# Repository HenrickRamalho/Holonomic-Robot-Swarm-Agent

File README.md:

# Omnino - Holonomic Agent for Swarm Robots

This project offers robotic technology for technical / scientific work in mobile robotics and swarm robots, using 3D printing tools, printed circuit board making, microcontroller programming, raspberry pi and the embedded implementation of ROS, you will be able to develop your own robotic agent and conduct your research in robotics on an experimental basis.

## Getting Started

To build this project, you must purchase the following bill of materials:

3 x Wheel Omni 1.5Pol

3 x Power Banck Pack for 2 Battery 18650

3 x Motor N20 6Vdc 90RPM and Encoder   

Print attached stl files

### Motor Speed Controller

The speed control of motors of a mobile robot is extremely important for the accomplishment of a good robotics project. This project involves the construction of a microcontrolled circuit for the speed control of each holonomic robot wheel, generating better performance of the position of the autonomous agent and the displacement controller.

"

### Prerequisites

What things you need to install the software and how to install them

```
Give examples
```

### Installing

A step by step series of examples that tell you how to get a development env running

Say what the step will be

```
Give the example
```

And repeat

```
until finished
```

End with an example of getting some data out of the system or using it for a little demo

## Running the tests

Explain how to run the automated tests for this system

### Break down into end to end tests

Explain what these tests test and why

```
Give an example
```

### And coding style tests

Explain what these tests test and why

```
Give an example
```

## Deployment

Add additional notes about how to deploy this on a live system

## Built With

* [Dropwizard](http://www.dropwizard.io/1.0.2/docs/) - The web framework used
* [Maven](https://maven.apache.org/) - Dependency Management
* [ROME](https://rometools.github.io/rome/) - Used to generate RSS Feeds

## Contributing

Please read [CONTRIBUTING.md](https://gist.github.com/PurpleBooth/b24679402957c63ec426) for details on our code of conduct, and the process for submitting pull requests to us.

## Versioning

We use [SemVer](http://semver.org/) for versioning. For the versions available, see the [tags on this repository](https://github.com/your/project/tags). 

## Authors

* **Henrick Ramalho** - *Initial work* - [PurpleBooth](https://github.com/PurpleBooth)

See also the list of [contributors](https://github.com/your/project/contributors) who participated in this project.

## License

This project is licensed under the MIT License - see the [LICENSE.md](LICENSE.md) file for details

## Acknowledgments

* Hat tip to anyone whose code was used
* Inspiration
* etc

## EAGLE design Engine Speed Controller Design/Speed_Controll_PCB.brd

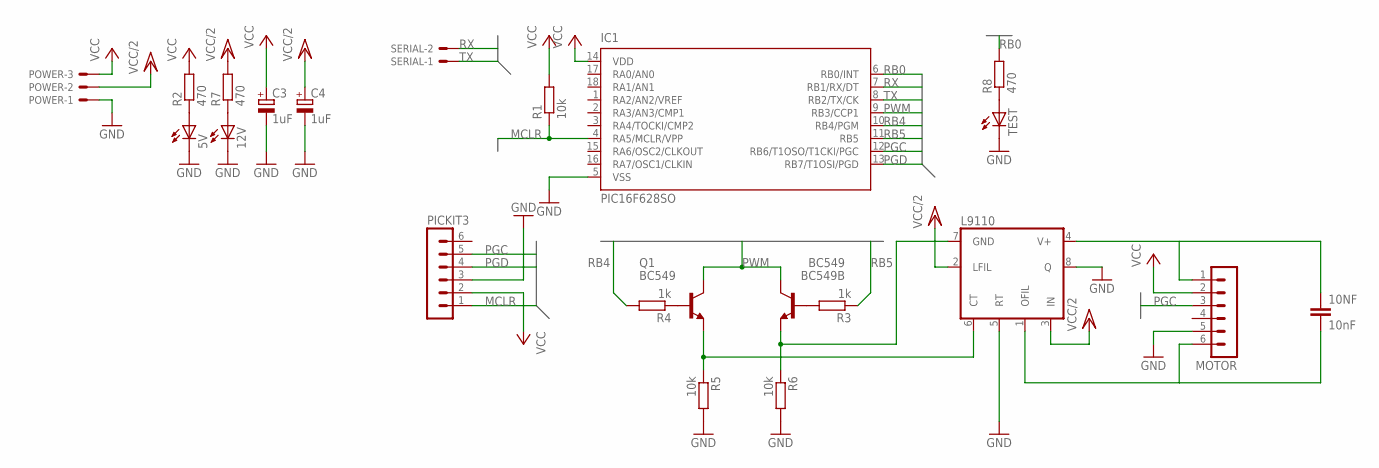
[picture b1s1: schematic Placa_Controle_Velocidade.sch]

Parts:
5V, 12V: LEDCHIPLED_1206; CHIPLED_1206
10NF: 10nF; C0603K
BC549: BC549B; TO92-EBC
C3, C4: 1uF; 153CLV-0405
IC1: PIC16F628SO; SO-18W
L9110: LM567D; SO08
MOTOR: MA06-1
PICKIT3: MA06-1
POWER: JST-XH-03-PIN-LONG-PAD; JST-XH-03-PACKAGE-LONG-PAD
Q1: BC549; TO92-EBC
R1, R5, R6: 10k; MINI_MELF-0102W
R2, R7, R8: 470; MINI_MELF-0102W
R3, R4: 1k; MINI_MELF-0102W
SERIAL: JST-XH-02-PIN-LONG-PAD; JST-XH-02-PACKAGE-LONG-PAD
TEST: LEDCHIPLED_1206; CHIPLED_1206

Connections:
GND: 5V.C, 12V.C, C3.-, C4.-, IC1.5 (VSS), L9110.5 (RT), L9110.8 (Q), MOTOR.5, PICKIT3.3, POWER.1, R5.2, R6.2, TEST.C
MCLR: IC1.4 (RA5/MCLR/VPP), PICKIT3.1, R1.1
unnamed: 10NF.1, L9110.4 (V+), MOTOR.1
unnamed: 5V.A, R2.1
unnamed: BC549.E, L9110.7 (GND), R6.1
unnamed: 10NF.2, L9110.1 (OFIL), MOTOR.6
unnamed: BC549.B, R3.2
unnamed: Q1.B, R4.1
unnamed: 12V.A, R7.1
unnamed: R8.1, TEST.A
unnamed: L9110.6 (CT), Q1.E, R5.1
PGC: IC1.12 (RB6/T1OSO/T1CKI/PGC), MOTOR.3, PICKIT3.5
PGD: IC1.13 (RB7/T1OSI/PGD), PICKIT3.4
PWM: BC549.C, IC1.9 (RB3/CCP1), Q1.C
RB0: IC1.6 (RB0/INT), R8.2
RB4: IC1.10 (RB4/PGM), R4.2
RB5: IC1.11 (RB5), R3.1
RX: IC1.7 (RB1/RX/DT), SERIAL.2
TX: IC1.8 (RB2/TX/CK), SERIAL.1
VCC: C3.+, IC1.14 (VDD), MOTOR.2, PICKIT3.2, POWER.3, R1.2, R2.2
VCC/2: C4.+, L9110.2 (LFIL), L9110.3 (IN), POWER.2, R7.2

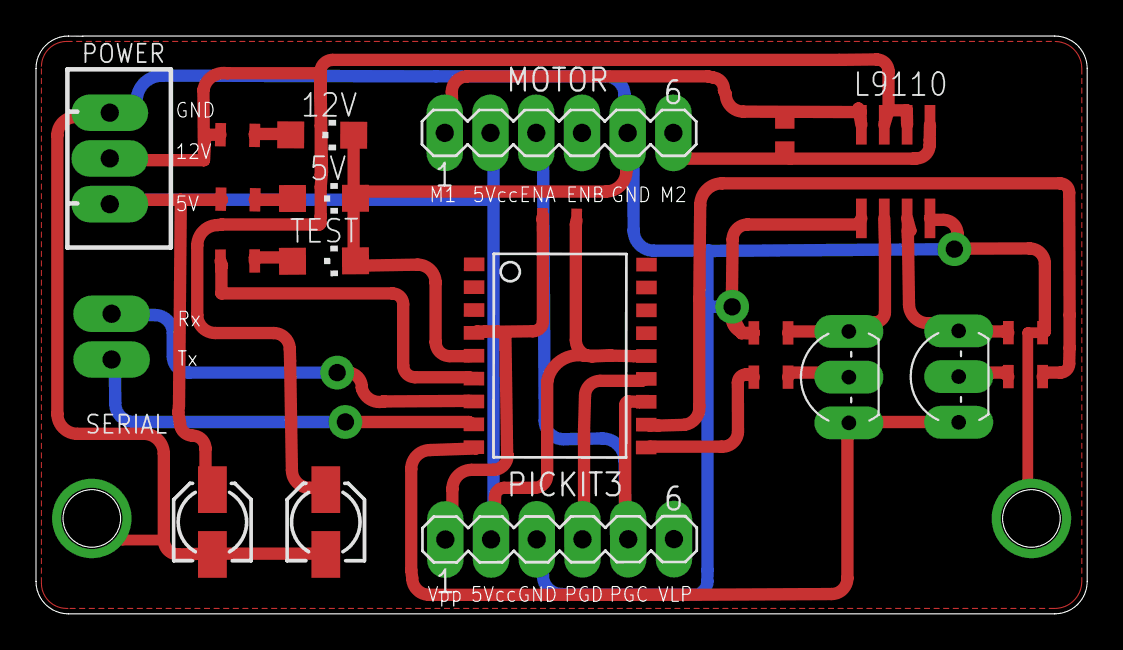
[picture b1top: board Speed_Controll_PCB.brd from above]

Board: 2 copper layers, 58.4 x 32.1 mm, 22 parts (1 on the bottom side), 21 nets.

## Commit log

2019-11-26 Create Engine Speed Controller
2019-11-26 Update Engine Speed Controller
2019-11-26 Create Motor Speed Controller
2020-02-06 add template for gazebo simulation
2020-02-18 Create STL File For Gazebo Simulation
2020-03-14 Adicionando Triangle Description Package
2020-04-30 Add files via upload
    This file can be opened with Eagle Autodesk.
